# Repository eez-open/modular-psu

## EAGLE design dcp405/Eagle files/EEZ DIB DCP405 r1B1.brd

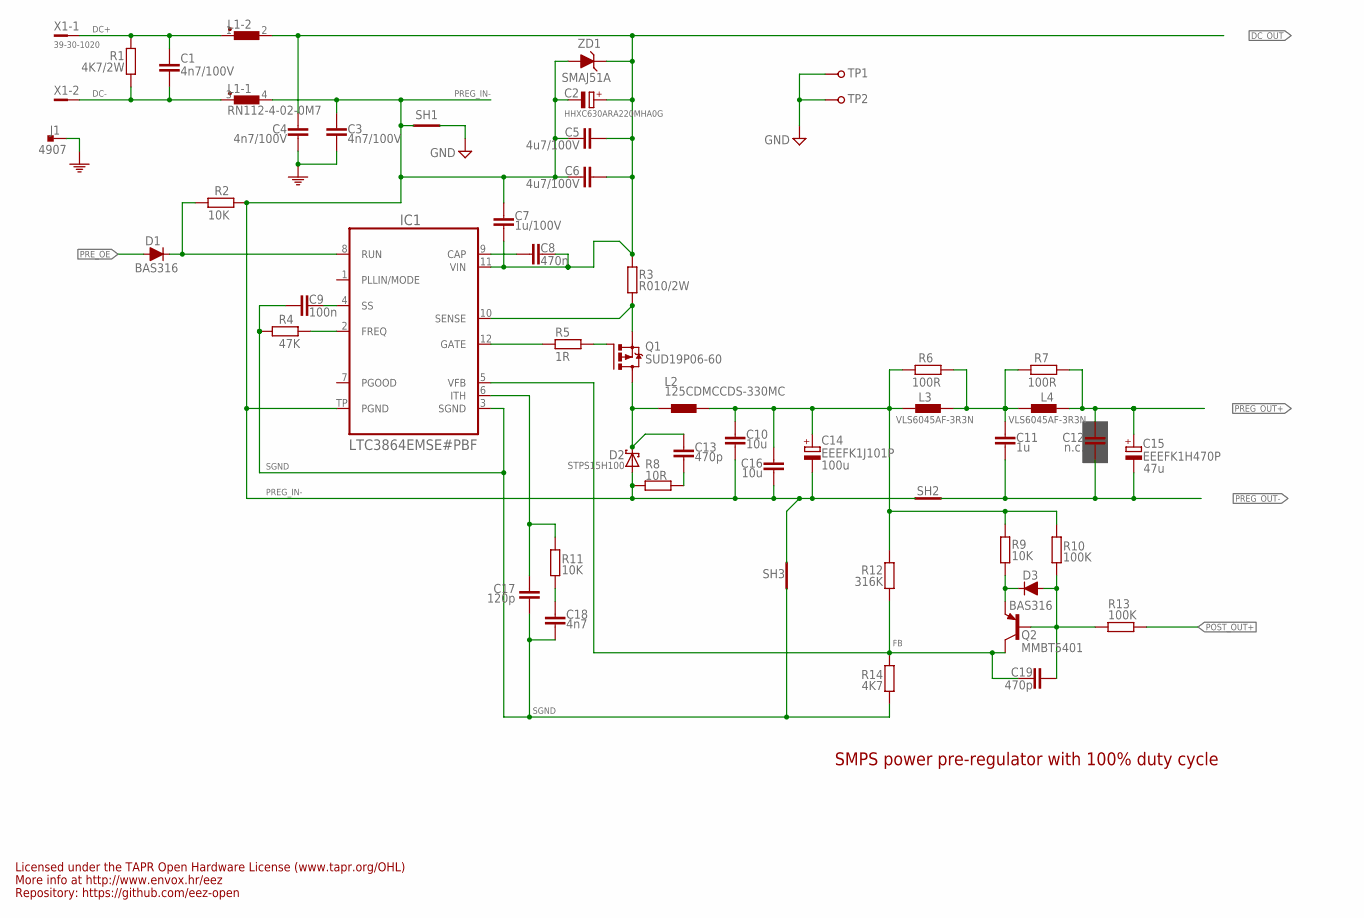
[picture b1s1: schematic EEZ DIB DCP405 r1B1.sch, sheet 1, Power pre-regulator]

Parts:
C1, C3, C4: 4n7/100V; C1206
C2: HHXC630ARA220MHA0G; CAPAE830X1050N
C5, C6: 4u7/100V; C1210
C7: 1u/100V; C1206
C8: 470n; C0805
C9: 100n; C0603
C10, C16: 10u; C1210
C11: 1u; C0805
C12: n.c.; C0805
C13, C19: 470p; C0805
C14: EEEFK1J101P; CAPAE1030X1050N
C15: EEEFK1H470P; CAPAE830X1050N
C17: 120p; C0805
C18: 4n7; C0805
D1, D3: BAS316; SOD323-R
D2: STPS15H100; TO252-L
IC1: LTC3864EMSE#PBF; LTC_05-08-1666
J1: 4907; PCB_TAB-4907
L1: RN112-4-02-0M7; RN112
L2: 125CDMCCDS-330MC; 125CDMCC/DS
L3, L4: VLS6045AF-3R3N; COILCRAFT_HPI0630
Q1: SUD19P06-60; TO229P990X239-3N
Q2: MMBT5401; SOT23-BEC
R1: 4K7/2W; R2512
R2, R9, R11: 10K; R0805
R3: R010/2W; R2512
R4: 47K; R0805
R5: 1R; R0805
R6, R7: 100R; R0805
R8: 10R; R1206
R10, R13: 100K; R0805
R12: 316K; R0805
R14: 4K7; R0805
SH1: SHORTNOHOLE; SHORT_NOHOLE
SH2: Pgnd to Pout- short; SHORT_NOHOLE
SH3: Sgnd to Pgnd short; SHORT_NOHOLE
TP1, TP2: PCB_TEST_TABSHIELD; PCB_SHIELD_TAB
X1: 39-30-1020; MINIFIT_39301020
ZD1: SMAJ51A; DO214AA

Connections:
DC+: C1.2, L1.1, R1.2, X1.1
DC-: C1.1, L1.3 (1), R1.1, X1.2
DC_OUT: C2.+, C4.2, C5.1, C6.1, C7.1, C8.2, IC1.11 (VIN), L1.2, R3.1, ZD1.C; also elsewhere on the board
FB: C19.1, IC1.5 (VFB), Q2.C, R12.2, R14.1
GND: SH1.2 (GND_B), TP1.1, TP2.1; also elsewhere on the board
L_OUT: C10.1, C14.+, C16.1, L2.2, L3.1, R6.1, R9.1, R10.1, R12.1
unnamed: D3.C, Q2.E, R9.2
unnamed: C18.1, R11.1
unnamed: D1.C, IC1.8 (RUN), R2.2
unnamed: C17.1, IC1.6 (ITH), R11.2
unnamed: C8.1, IC1.9 (CAP)
unnamed: IC1.2 (FREQ), R4.1
unnamed: C9.2, IC1.4 (SS)
unnamed: Q1.1 (G), R5.2
unnamed: IC1.12 (GATE), R5.1
unnamed: C11.1, L3.2, L4.1, R6.2, R7.1
unnamed: C13.2, R8.2
unnamed: C19.2, D3.A, Q2.B, R10.2, R13.1
PE: C3.2, C4.1, J1.1, J1.2; also elsewhere on the board
POST_OUT+: R13.2; also elsewhere on the board
PREG_IN-: C2.-, C3.1, C5.2, C6.2, C7.2, C10.2, C14.-, C16.2, D2.1 (A), D2.2 (A), IC1.TP (PGND), L1.4 (2), R2.1, R8.1, SH1.1 (GND_A), SH2.2 (GND_B), SH3.2 (GND_B), ZD1.A
PREG_OUT+: C12.1, C15.+, L4.2, R7.2; also elsewhere on the board
PREG_OUT-: C11.2, C12.2, C15.-, SH2.1 (GND_A); also elsewhere on the board
PRE_OE: D1.A; also elsewhere on the board
SENSE: IC1.10 (SENSE), Q1.3 (S), R3.2
SGND: C9.1, C17.2, C18.2, IC1.3 (SGND), R4.2, R14.2, SH3.1 (GND_A)
SW: C13.1, D2.3 (C), L2.1, Q1.2 (D)

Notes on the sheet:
47u
Licensed under the TAPR Open Hardware License (www.tapr.org/OHL)
Repository: https://github.com/eez-open
More info at http://www.envox.hr/eez
SMPS power pre-regulator with 100% duty cycle
100u

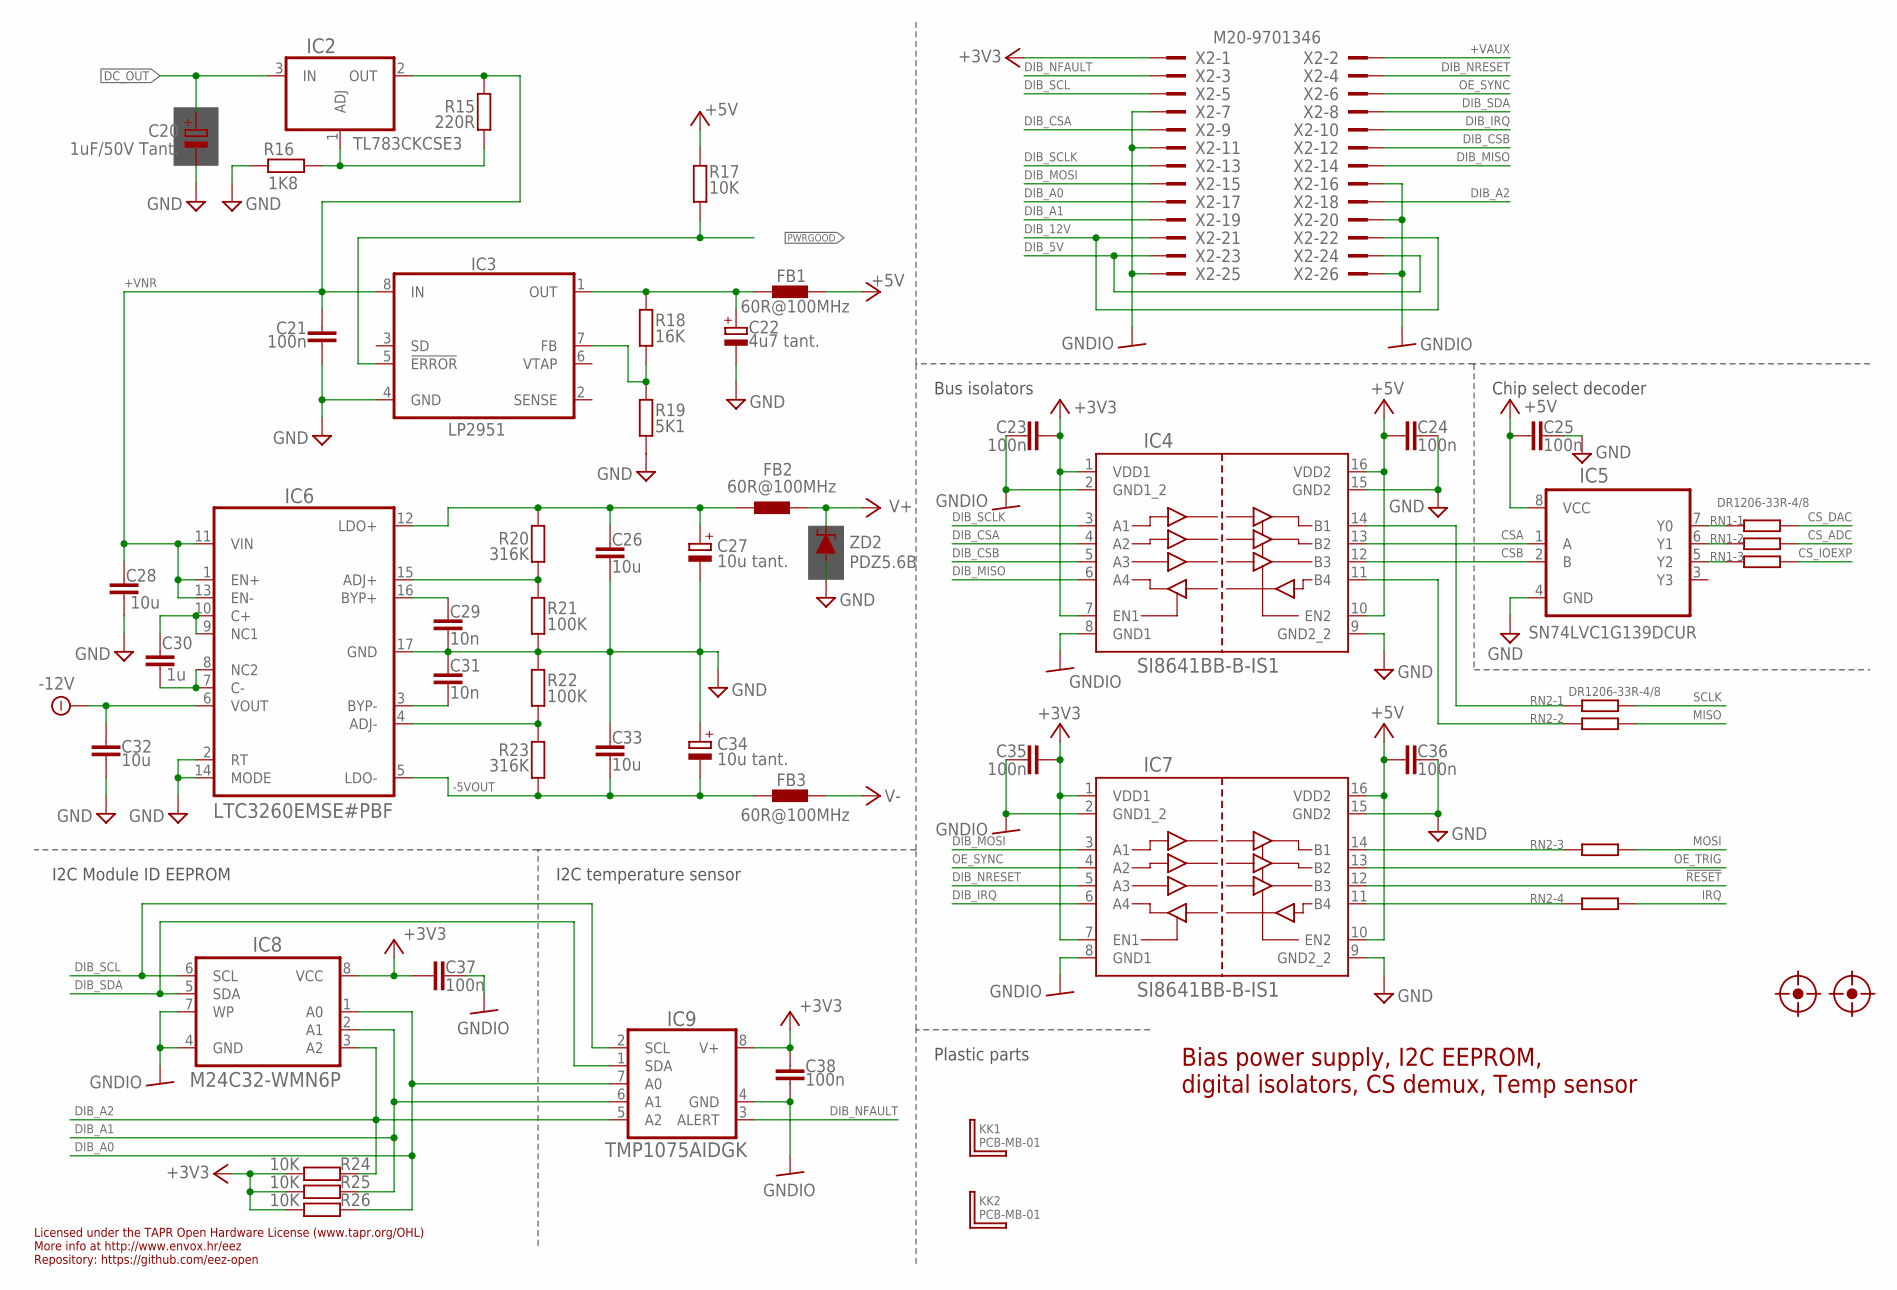
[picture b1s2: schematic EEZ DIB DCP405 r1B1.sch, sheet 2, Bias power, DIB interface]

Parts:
C20: 1uF/50V Tant.; C/6032-28R
C21, C23, C24, C25, C35, C36, C37, C38: 100n; C0603
C22: 4u7 tant.; EC1206
C26, C28, C32, C33: 10u; C1210
C27, C34: 10u tant.; EC1206
C29, C31: 10n; C0805
C30: 1u; C0805
FB1, FB2, FB3: 60R@100MHz; BEAD0603
FM1, FM2: FIDUCIAL_2; FIDUCIAL_DUAL
IC2: TL783CKCSE3; TO220H-CLR2
IC3: LP2951; SOIC127P600X175-8N
IC4, IC7: SI8641BB-B-IS1; SOIC-16
IC5: SN74LVC1G139DCUR; DCU8
IC6: LTC3260EMSE#PBF; SOP50P490X110-17N
IC8: M24C32-WMN6P; SOIC127P600X173-8N
IC9: TMP1075AIDGK; DGK8
KK1, KK2: PCB-MB-01; PCB-MB
R15: 220R; R0805
R16: 1K8; R0805
R17, R24, R25, R26: 10K; R0805
R18: 16K; R0805
R19: 5K1; R0805
R20, R23: 316K; R0805
R21, R22: 100K; R0805
RN1, RN2: DR1206-33R-4/8; CAY16
X2: M20-9701346
ZD2: PDZ5.6B; SOD323-W

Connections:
!RESET: IC7.12 (B3); also elsewhere on the board
+3V3: C23.1, C35.1, C37.2, C38.1, IC4.1 (VDD1), IC4.7 (EN1), IC7.1 (VDD1), IC7.7 (EN1), IC8.8 (VCC), IC9.8 (V+), R24.1, R25.1, R26.1, X2.1
+5V: C24.2, C25.1, C36.2, FB1.P$2 (2), IC4.10 (EN2), IC4.16 (VDD2), IC5.8 (VCC), IC7.10 (EN2), IC7.16 (VDD2), R17.1; also elsewhere on the board
+5VOUT: C26.1, C27.+, FB2.P$1 (1), IC6.12 (LDO+), R20.1
+VAUX: X2.2
+VNR: C21.1, C28.1, IC2.2 (OUT), IC3.8 (IN), IC6.1 (EN+), IC6.11 (VIN), IC6.13 (EN-), R15.1
-5VOUT: C33.2, C34.-, FB3.P$1 (1), IC6.5 (LDO-), R23.2
-12V: C32.1, IC6.6 (VOUT); also elsewhere on the board
CSA: IC4.13 (B2), IC5.1 (A)
CSB: IC4.12 (B3), IC5.2 (B)
CS_ADC: RN1.7 (2); also elsewhere on the board
CS_DAC: RN1.8 (2); also elsewhere on the board
CS_IOEXP: RN1.6 (2); also elsewhere on the board
DC_OUT: C20.+, IC2.3 (IN); also elsewhere on the board
DIB_5V: X2.23, X2.24
DIB_12V: X2.21, X2.22
DIB_A0: IC8.1 (A0), IC9.7 (A0), R26.2, X2.17
DIB_A1: IC8.2 (A1), IC9.6 (A1), R25.2, X2.19
DIB_A2: IC8.3 (A2), IC9.5 (A2), R24.2, X2.18
DIB_CSA: IC4.4 (A2), X2.9
DIB_CSB: IC4.5 (A3), X2.12
DIB_IRQ: IC7.6 (A4), X2.10
DIB_MISO: IC4.6 (A4), X2.14
DIB_MOSI: IC7.3 (A1), X2.15
DIB_NFAULT: IC9.3 (ALERT), X2.3
DIB_NRESET: IC7.5 (A3), X2.4
DIB_SCL: IC8.6 (SCL), IC9.2 (SCL), X2.5
DIB_SCLK: IC4.3 (A1), X2.13
DIB_SDA: IC8.5 (SDA), IC9.1 (SDA), X2.8
GND: C20.-, C21.2, C22.-, C24.1, C25.2, C26.2, C27.-, C28.2, C29.1, C31.1, C32.2, C33.1, C34.+, C36.1, IC3.4 (GND), IC4.9 (GND2_2), IC4.15 (GND2), IC5.4 (GND), IC6.2 (RT), IC6.14 (MODE), IC6.17 (GND), IC7.9 (GND2_2), IC7.15 (GND2), R16.2, R19.2, R21.2, R22.1, ZD2.A; also elsewhere on the board
GNDIO: C23.2, C35.2, C37.1, C38.2, IC4.2 (GND1_2), IC4.8 (GND1), IC7.2 (GND1_2), IC7.8 (GND1), IC8.4 (GND), IC8.7 (WP), IC9.4 (GND), X2.7, X2.11, X2.16, X2.20, X2.25, X2.26
IRQ: RN2.5 (2); also elsewhere on the board
MISO: RN2.7 (2); also elsewhere on the board
MOSI: RN2.6 (2); also elsewhere on the board
unnamed: IC5.5 (Y2), RN1.3 (1)
unnamed: IC5.7 (Y0), RN1.1
unnamed: IC4.11 (B4), RN2.2 (1)
unnamed: IC7.11 (B4), RN2.4 (1)
unnamed: IC5.6 (Y1), RN1.2 (1)
unnamed: IC6.15 (ADJ+), R20.2, R21.1
unnamed: C30.1, IC6.9 (NC1), IC6.10 (C+)
unnamed: C30.2, IC6.7 (C-), IC6.8 (NC2)
unnamed: C29.2, IC6.16 (BYP+)
unnamed: IC6.4 (ADJ-), R22.2, R23.1
unnamed: C31.2, IC6.3 (BYP-)
unnamed: IC7.14 (B1), RN2.3 (1)
unnamed: IC3.7 (FB), R18.2, R19.1
unnamed: IC4.14 (B1), RN2.1
unnamed: C22.+, FB1.P$1 (1), IC3.1 (OUT), R18.1
OE_SYNC: IC7.4 (A2), X2.6
OE_TRIG: IC7.13 (B2); also elsewhere on the board
PWRGOOD: IC3.5 (!ERROR), R17.2; also elsewhere on the board
SCLK: RN2.8 (2); also elsewhere on the board
TL783_ADJ: IC2.1 (ADJ), R15.2, R16.1
V+: FB2.P$2 (2), ZD2.C; also elsewhere on the board
V-: FB3.P$2 (2); also elsewhere on the board

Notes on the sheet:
Licensed under the TAPR Open Hardware License (www.tapr.org/OHL)
Repository: https://github.com/eez-open
More info at http://www.envox.hr/eez
I2C Module ID EEPROM
Bus isolators
Bias power supply, I2C EEPROM, digital isolators, CS demux, Temp sensor
Plastic parts
Chip select decoder
I2C temperature sensor

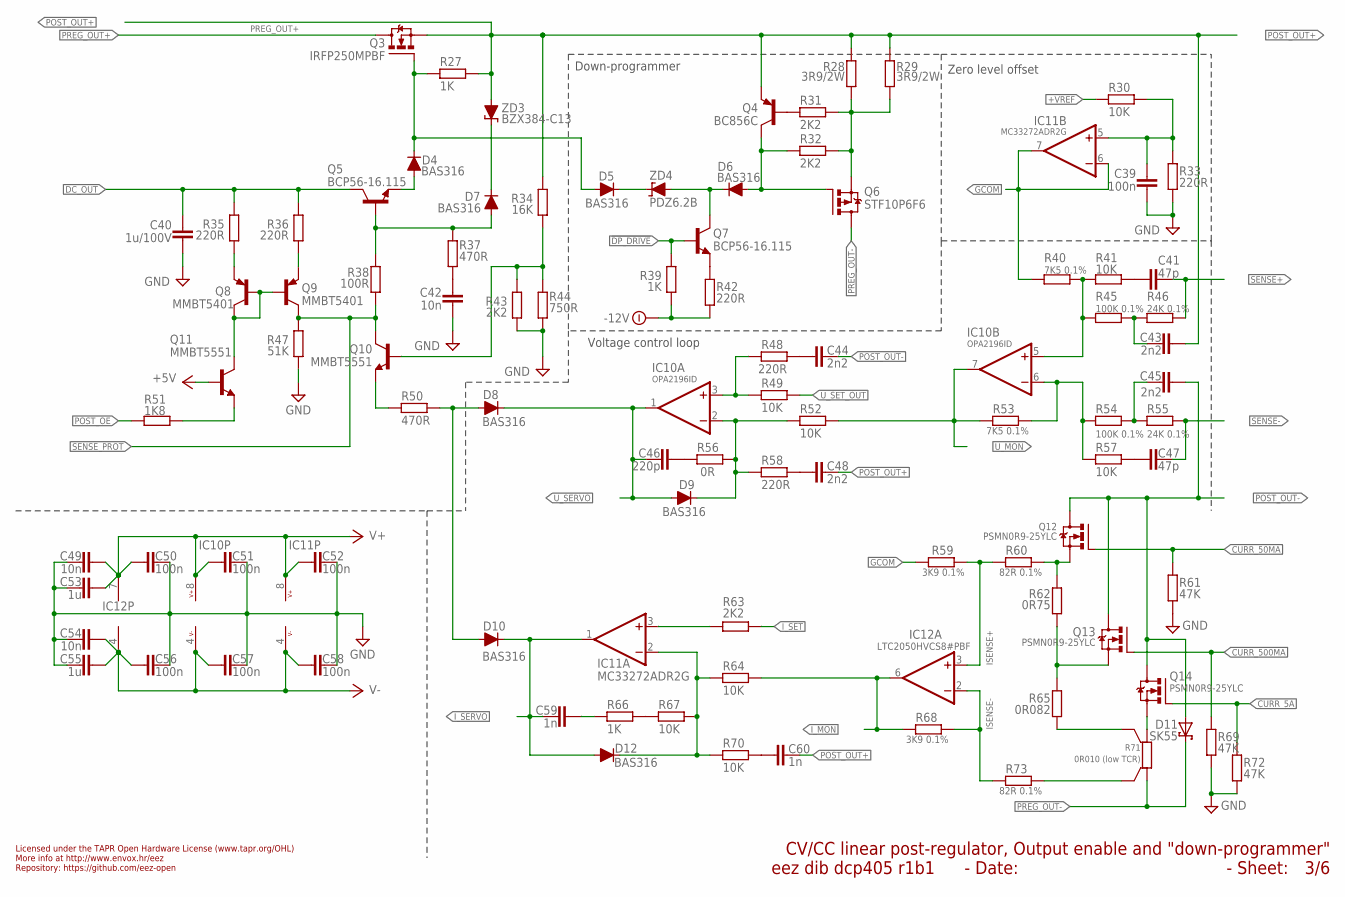
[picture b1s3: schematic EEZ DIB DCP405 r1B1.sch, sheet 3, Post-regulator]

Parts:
C39, C50, C51, C52, C56, C57, C58: 100n; C0603
C40: 1u/100V; C1206
C41, C47: 47p; C0805
C42, C49, C54: 10n; C0805
C43, C44, C45, C48: 2n2; C0805
C46: 220p; C0805
C53, C55: 1u; C0805
C59, C60: 1n; C0805
D4, D5, D6, D7, D8, D9, D10, D12: BAS316; SOD323-R
D11: SK55; SMB
IC10: OPA2196ID; SOIC127P600X173-8N
IC11: MC33272ADR2G; SOIC127P600X173-8N
IC12: LTC2050HVCS8#PBF; SOIC127P600X173-8N
Q3: IRFP250MPBF; TO247BH-CLR2
Q4: BC856C; SOT23-BEC
Q5, Q7: BCP56-16.115; SOT230P700X180-4N
Q6: STF10P6F6; TO220H-CLR2
Q8, Q9: MMBT5401; SOT23-BEC
Q10, Q11: MMBT5551; SOT23-BEC
Q12, Q13, Q14: PSMN0R9-25YLC; SOT669
R27, R39, R66: 1K; R0805
R28, R29: 3R9/2W; R2512
R30, R41, R49, R52, R57, R64, R67, R70: 10K; R0805
R31, R32, R43, R63: 2K2; R0805
R33, R35, R36, R42, R48, R58: 220R; R0805
R34: 16K; R0805
R37, R50: 470R; R0805
R38: 100R; R0805
R40, R53: 7K5 0.1%; R0805
R44: 750R; R0805
R45, R54: 100K 0.1%; R0805
R46, R55: 24K 0.1%; R0805
R47: 51K; R0805
R51: 1K8; R0805
R56: 0R; R0805
R59, R68: 3K9 0.1%; R0805
R60, R73: 82R 0.1%; R0805
R61, R69, R72: 47K; R0805
R62: 0R75; R1206
R65: 0R082; R1210
R71: 0R010 (low TCR); R_H2728
ZD3: BZX384-C13; SOD323-W
ZD4: PDZ6.2B; SOD323-W

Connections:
5A_S: Q14.1 (S), Q14.2 (S), Q14.3 (S), R71.2
50MA_S: Q12.1 (S), Q12.2 (S), Q12.3 (S), R60.1, R62.1
500MA_S: Q13.1 (S), Q13.2 (S), Q13.3 (S), R62.2, R65.2
!DP_DRIVE: Q7.1 (B), R39.1; also elsewhere on the board
+5V: Q11.B; also elsewhere on the board
+VREF: R30.1; also elsewhere on the board
-12V: R39.2, R42.2; also elsewhere on the board
CURR_5A: Q14.4 (G), R72.2; also elsewhere on the board
CURR_50MA: Q12.4 (G), R61.2; also elsewhere on the board
CURR_500MA: Q13.4 (G), R69.2; also elsewhere on the board
DC_OUT: C40.1, Q5.2 (C), Q5.4 (C), R35.2, R36.2; also elsewhere on the board
DP_S: Q6.3 (S), R28.1, R29.1, R31.1, R32.1
GCOM: IC11.6 (-IN), IC11.7 (OUT), R40.1, R59.1
GND: C39.2, C40.2, C42.2, C49.1, C50.2, C51.1, C52.1, C53.1, C54.1, C55.1, C56.2, C57.1, C58.1, R33.2, R43.1, R44.1, R47.1, R61.1, R69.1, R72.1; also elsewhere on the board
ISENSE+: IC12.3 (+IN), R59.2, R60.2
ISENSE-: IC12.2 (-IN), R68.1, R73.2
I_MON: IC12.6 (OUT), R64.1, R68.2; also elsewhere on the board
I_SERVO: C59.2, D10.C, D12.A, IC11.1 (OUT); also elsewhere on the board
I_SET: R63.1; also elsewhere on the board
LOOP_CTRL: D8.A, D10.A, R50.1
unnamed: R65.1, R71.2S
unnamed: C46.1, R56.2
unnamed: IC11.3 (+IN), R63.2
unnamed: IC10.3 (+IN), R48.2, R49.2
unnamed: D9.C, IC10.2 (-IN), R52.2, R56.1, R58.2
unnamed: C45.1, R54.2, R55.1
unnamed: C41.2, R41.1
unnamed: C47.2, R57.1
unnamed: C60.2, R70.1
unnamed: D12.C, IC11.2 (-IN), R64.2, R67.2, R70.2
unnamed: C44.2, R48.1
unnamed: C48.2, R58.1
unnamed: D4.C, D5.A, Q3.1 (G), R27.1
unnamed: D4.A, Q5.3 (E)
unnamed: D7.A, Q5.1 (B), R37.2, R38.1
unnamed: C42.1, R37.1
unnamed: Q10.B, R34.1, R43.2, R44.2
unnamed: Q7.3 (E), R42.1
unnamed: Q4.B, R31.2
unnamed: C39.1, IC11.5 (+IN), R30.2, R33.1
unnamed: C43.1, R45.2, R46.1
unnamed: D7.C, ZD3.C
unnamed: D5.C, ZD4.C
unnamed: Q10.E, R50.2
unnamed: D6.A, Q4.C, Q6.1 (G), R32.2
unnamed: IC10.5 (+IN), R40.2, R41.2, R45.1
unnamed: IC10.6 (-IN), R53.2, R54.1, R57.2
unnamed: R66.2, R67.1
unnamed: C59.1, R66.1
unnamed: Q9.E, R36.1
unnamed: Q8.E, R35.1
unnamed: Q11.E, R51.2
unnamed: R71.1S, R73.1
POST_OE: R51.1; also elsewhere on the board
POST_OUT+: C43.2, C48.1, C60.1, Q3.3 (S), Q4.E, R27.2, R28.2, R29.2, R34.2, ZD3.A; also elsewhere on the board
POST_OUT-: C44.1, C45.2, D11.A, Q12.MB (D), Q13.MB (D), Q14.MB (D); also elsewhere on the board
PREG_OUT+: Q3.2 (D); also elsewhere on the board
PREG_OUT-: D11.C, Q6.2 (D), R71.1; also elsewhere on the board
Q6C: D6.C, Q7.2 (C), Q7.4 (C), ZD4.A
Q7C: Q8.B, Q8.C, Q9.B, Q11.C
SENSE+: C41.1, R46.2; also elsewhere on the board
SENSE-: C47.1, R55.2; also elsewhere on the board
SENSE_PROT: Q9.C, Q10.C, R38.2, R47.2; also elsewhere on the board
U_MON: IC10.7 (OUT), R52.1, R53.1; also elsewhere on the board
U_SERVO: C46.2, D8.C, D9.A, IC10.1 (OUT); also elsewhere on the board
U_SET_OUT: R49.1; also elsewhere on the board
V+: C49.2, C50.1, C51.2, C52.2, C53.2, IC10.8 (V+), IC11.8 (V+), IC12.7 (V+); also elsewhere on the board
V-: C54.2, C55.2, C56.1, C57.2, C58.2, IC10.4 (V-), IC11.4 (V-), IC12.4 (V-); also elsewhere on the board

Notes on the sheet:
Voltage control loop
Down-programmer
Licensed under the TAPR Open Hardware License (www.tapr.org/OHL)
Repository: https://github.com/eez-open
More info at http://www.envox.hr/eez
Zero level offset
CV/CC linear post-regulator, Output enable and "down-programmer"
- Sheet:
- Date:

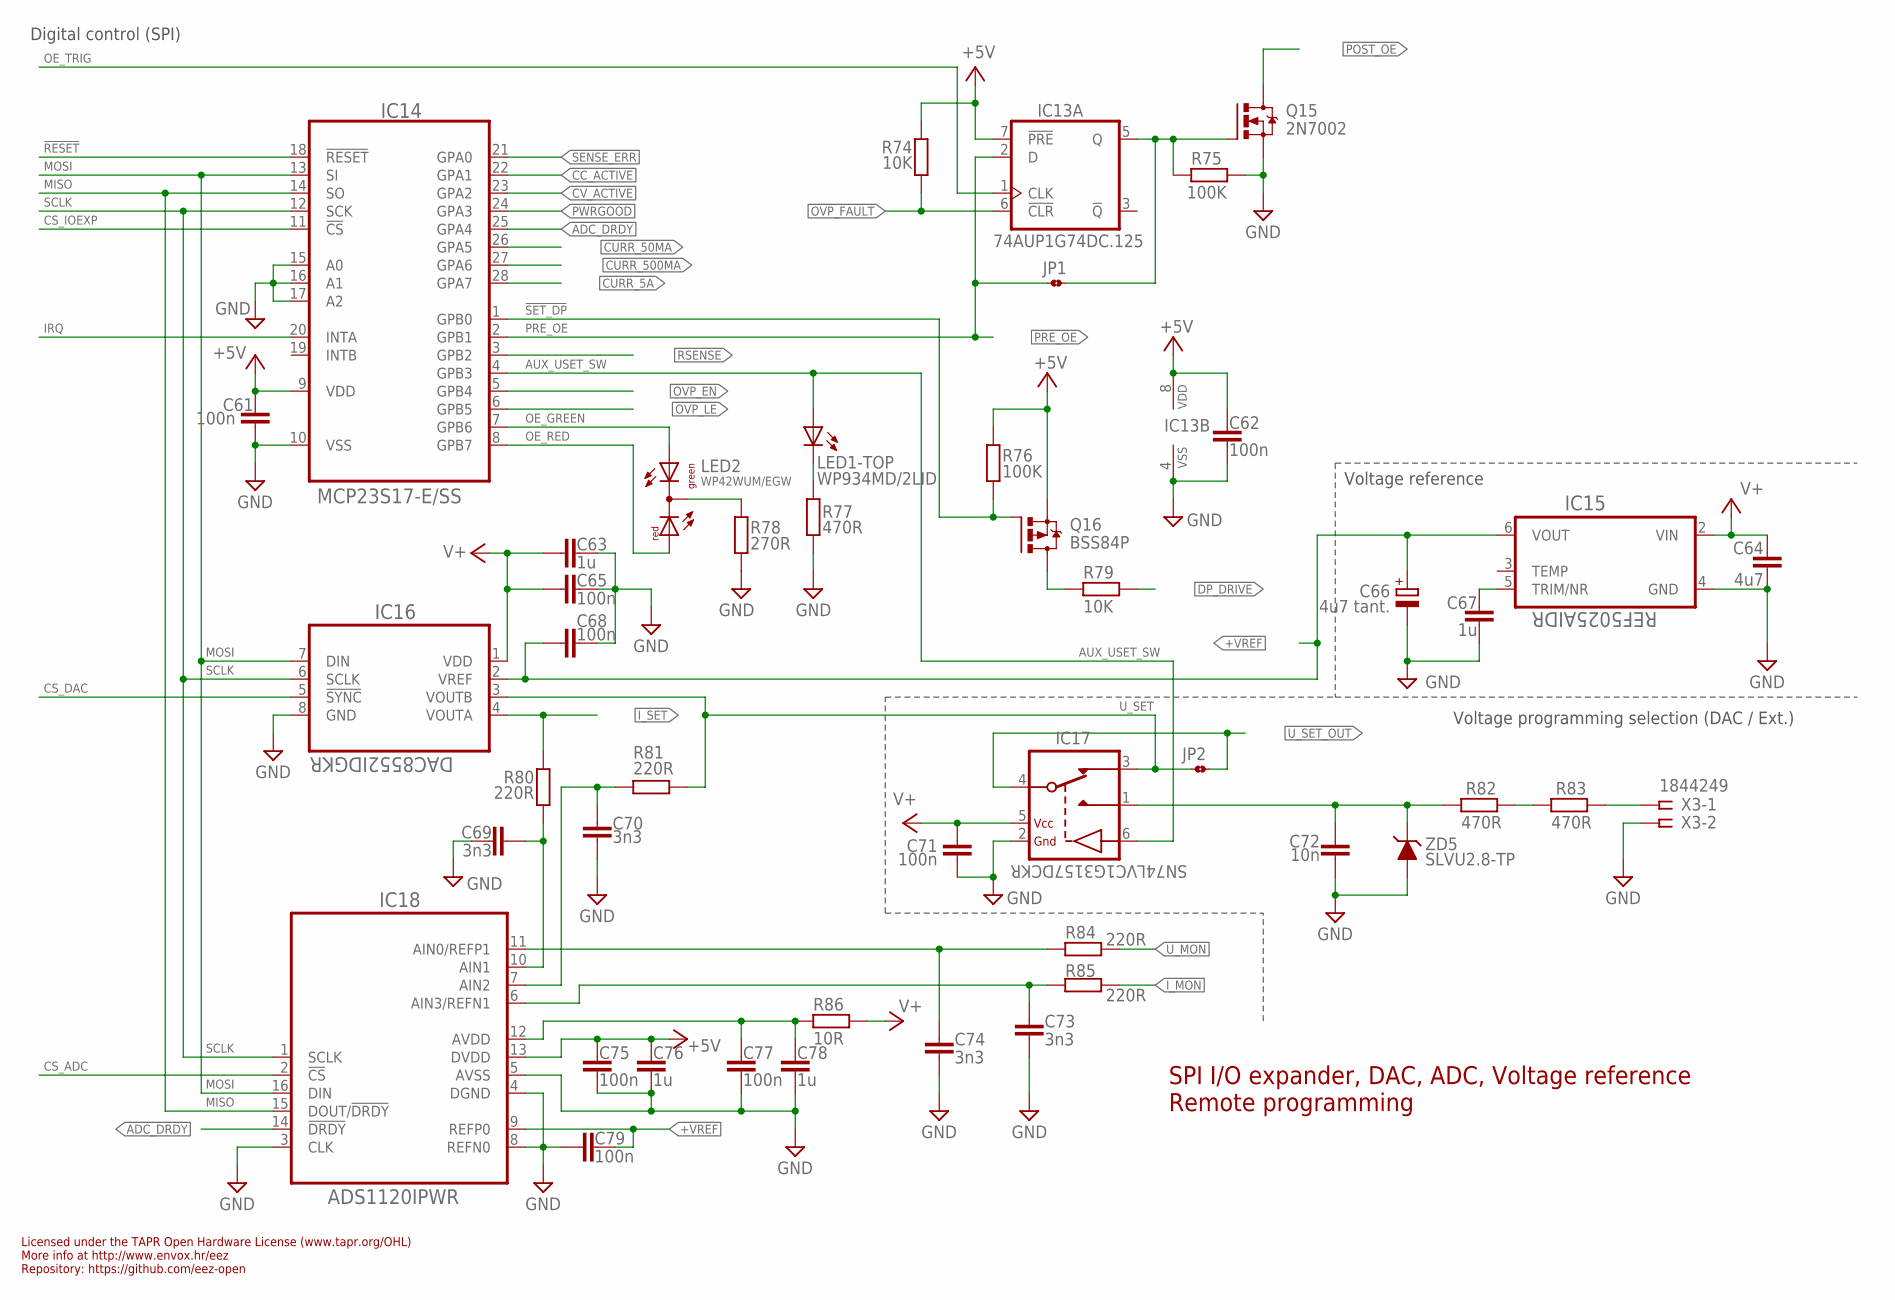
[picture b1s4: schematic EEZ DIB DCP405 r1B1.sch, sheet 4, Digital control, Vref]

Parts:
C61, C62, C65, C68, C71, C75, C77, C79: 100n; C0603
C63, C67, C76, C78: 1u; C0805
C64: 4u7; C1206
C66: 4u7 tant.; EC1206
C69, C70, C73, C74: 3n3; C0805
C72: 10n; C0805
IC13: 74AUP1G74DC.125; DCU8
IC14: MCP23S17-E/SS; SOP65P780X200-28N
IC15: REF5025AIDR; SOIC127P600X175-8N
IC16: DAC8552IDGKR; DGK8-M
IC17: SN74LVC1G3157DCKR; SOT65P210X110-6N
IC18: ADS1120IPWR; PW(R-PDSO-G16)
JP1, JP2: JP2-CUT
LED1: WP934MD/2LID; WP934MD
LED2: WP42WUM/EGW; L-42WUM-1EGWT
Q15: 2N7002; SOT103P240X110-3N; MPN 2N7002-7-F
Q16: BSS84P; SOT95P237X112-3N
R74, R79: 10K; R0805
R75, R76: 100K; R0805
R77, R82, R83: 470R; R0805
R78: 270R; R0805
R80, R81, R84, R85: 220R; R0805
R86: 10R; R1206
X3: 1844249; MC1,5/5-G-3,5
ZD5: SLVU2.8-TP; SOT23

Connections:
!ADC_DRDY: IC14.25 (GPA4), IC18.14 (!DRDY)
!DP_DRIVE: R79.1; also elsewhere on the board
!OVP_FAULT: IC13.6 (!CLR), R74.2; also elsewhere on the board
!OVP_LE: IC14.6 (GPB5); also elsewhere on the board
!RESET: IC14.18 (!RESET); also elsewhere on the board
!SET_DP: IC14.1 (GPB0), Q16.1 (G), R76.2
+5V: C61.1, C62.2, C75.2, C76.2, IC13.7 (!PRE), IC13.8 (VDD), IC14.9 (VDD), IC18.13 (DVDD), Q16.2 (S), R74.1, R76.1; also elsewhere on the board
+VREF: C66.+, C68.2, C79.2, IC15.6 (VOUT), IC16.2 (VREF), IC18.9 (REFP0); also elsewhere on the board
AUX_IN: C72.2, IC17.1 (NO), R82.1, ZD5.3 (C)
AUX_USET_SW: IC14.4 (GPB3), IC17.6 (CTRL), LED1.TA (A)
CC_ACTIVE: IC14.22 (GPA1); also elsewhere on the board
CS_ADC: IC18.2 (!CS); also elsewhere on the board
CS_DAC: IC16.5 (!SYNC); also elsewhere on the board
CS_IOEXP: IC14.11 (!CS); also elsewhere on the board
CURR_5A: IC14.28 (GPA7); also elsewhere on the board
CURR_50MA: IC14.26 (GPA5); also elsewhere on the board
CURR_500MA: IC14.27 (GPA6); also elsewhere on the board
CV_ACTIVE: IC14.23 (GPA2); also elsewhere on the board
DP_LED: Q16.3 (D), R79.2
GND: C61.2, C62.1, C63.2, C64.2, C65.1, C66.-, C67.2, C68.1, C69.1, C70.1, C71.2, C72.1, C73.2, C74.1, C75.1, C76.1, C77.1, C78.1, C79.1, IC13.4 (VSS), IC14.10 (VSS), IC14.15 (A0), IC14.16 (A1), IC14.17 (A2), IC15.4 (GND), IC16.8 (GND), IC17.2 (GND), IC18.3 (CLK), IC18.4 (DGND), IC18.5 (AVSS), IC18.8 (REFN0), Q15.2 (S), R75.1, R77.1, R78.2, X3.2, ZD5.1 (A), ZD5.2 (A); also elsewhere on the board
IRQ: IC14.20 (INTA); also elsewhere on the board
I_MON: R85.1; also elsewhere on the board
I_SET: IC16.4 (VOUTA), R80.1; also elsewhere on the board
MISO: IC14.14 (SO), IC18.15 (DOUT/!DRDY); also elsewhere on the board
MOSI: IC14.13 (SI), IC16.7 (DIN), IC18.16 (DIN); also elsewhere on the board
unnamed: LED2.CC (C), R78.1
unnamed: R82.2, R83.1
unnamed: R83.2, X3.1
unnamed: IC13.5 (Q), JP1.2, Q15.1 (G), R75.2
unnamed: C77.2, C78.2, IC18.12 (AVDD), R86.2
unnamed: C67.1, IC15.5 (TRIM/NR)
unnamed: C69.2, IC18.10 (AIN1), R80.2
unnamed: C74.2, IC18.11 (AIN0/REFP1), R84.2
unnamed: C70.2, IC18.7 (AIN2), R81.2
unnamed: C73.1, IC18.6 (AIN3/REFN1), R85.2
unnamed: LED1.TC (C), R77.2
OE_GREEN: IC14.7 (GPB6), LED2.GREEN (AG)
OE_RED: IC14.8 (GPB7), LED2.RED (AR)
OE_TRIG: IC13.1 (CLK); also elsewhere on the board
OVP_EN: IC14.5 (GPB4); also elsewhere on the board
POST_OE: Q15.3 (D); also elsewhere on the board
PRE_OE: IC13.2 (D), IC14.2 (GPB1), JP1.1; also elsewhere on the board
PWRGOOD: IC14.24 (GPA3); also elsewhere on the board
RSENSE: IC14.3 (GPB2); also elsewhere on the board
SCLK: IC14.12 (SCK), IC16.6 (SCLK), IC18.1 (SCLK); also elsewhere on the board
SENSE_ERR: IC14.21 (GPA0); also elsewhere on the board
U_MON: R84.1; also elsewhere on the board
U_SET: IC16.3 (VOUTB), IC17.3 (NC), JP2.1, R81.1; also elsewhere on the board
U_SET_OUT: IC17.4 (COM), JP2.2; also elsewhere on the board
V+: C63.1, C64.1, C65.2, C71.1, IC15.2 (VIN), IC16.1 (VDD), IC17.5 (VDD), R86.1; also elsewhere on the board

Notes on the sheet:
SPI I/O expander, DAC, ADC, Voltage reference
Digital control (SPI)
Voltage reference
Licensed under the TAPR Open Hardware License (www.tapr.org/OHL)
Repository: https://github.com/eez-open
More info at http://www.envox.hr/eez
Remote programming
Voltage programming selection (DAC / Ext.)

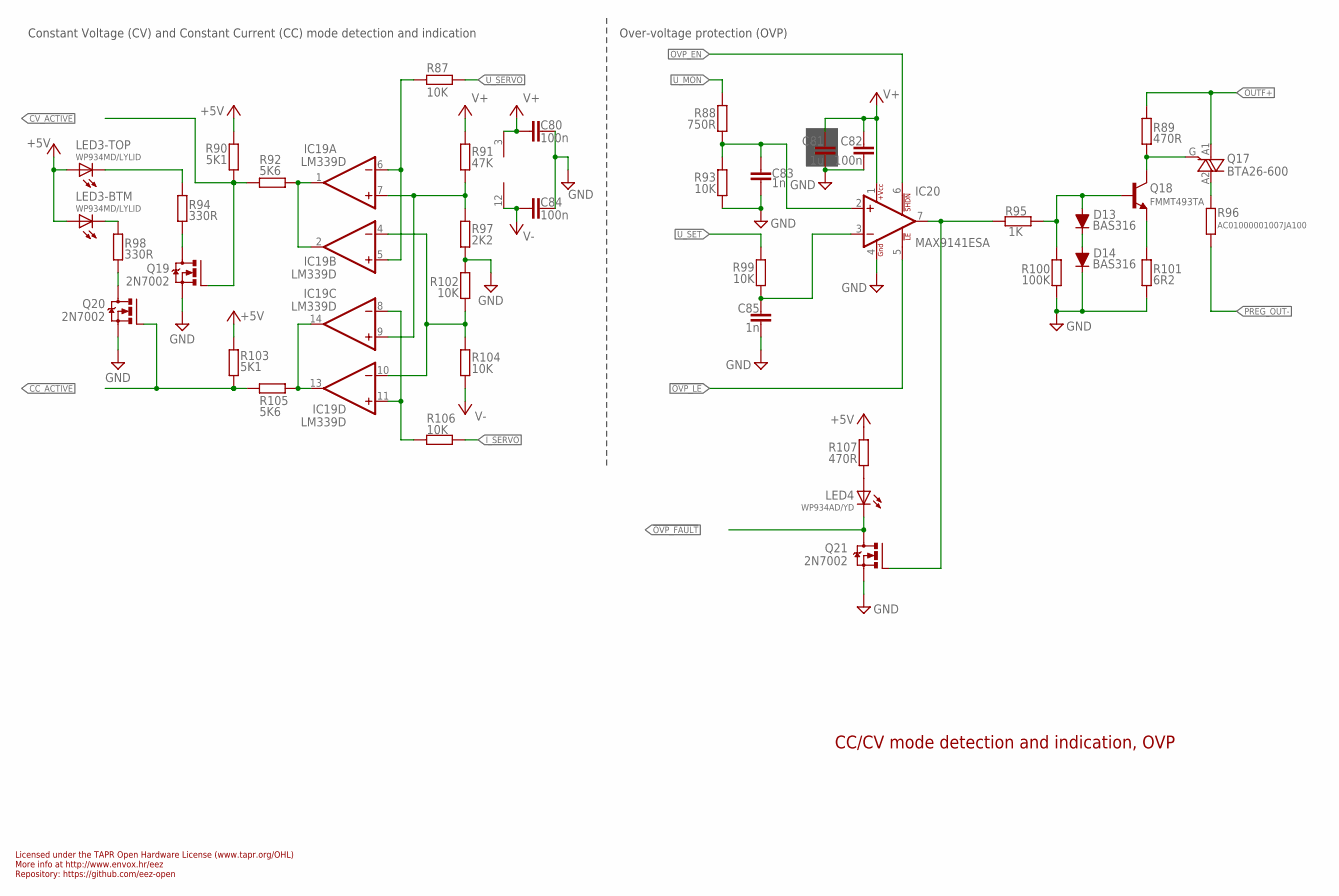
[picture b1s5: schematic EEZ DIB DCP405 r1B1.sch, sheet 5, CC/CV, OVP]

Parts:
C80, C82, C84: 100n; C0603
C81: 1u; C0805
C83, C85: 1n; C0805
D13, D14: BAS316; SOD323-R
IC19: LM339D; SOIC127P600X175-14N
IC20: MAX9141ESA; SOIC127P600X173-8N
LED3: WP934MD/LYLID; WP934MD
LED4: WP934AD/YD; WP934AD
Q17: BTA26-600; TOP3_TRIAC_NOHOLE
Q18: FMMT493TA; SOT23-BEC
Q19, Q20: 2N7002; SOT103P240X110-3N
Q21: 2N7002; SOT103P240X110-3N; MPN 2N7002-7-F
R87, R93, R99, R102, R104, R106: 10K; R0805
R88: 750R; R0805
R89, R107: 470R; R0805
R90, R103: 5K1; R0805
R91: 47K; R0805
R92, R105: 5K6; R0805
R94, R98: 330R; R0805
R95: 1K; R0805
R96: AC01000001007JA100; 0411/15
R97: 2K2; R0805
R100: 100K; R0805
R101: 6R2; R0805

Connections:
!OVP_FAULT: LED4.C, Q21.3 (D); also elsewhere on the board
!OVP_LE: IC20.5 (!LE); also elsewhere on the board
+5V: LED3.BA (A), LED3.TA (A), R90.2, R103.2, R107.1; also elsewhere on the board
CC_ACTIVE: Q20.1 (G), R103.1, R105.2; also elsewhere on the board
CC_LED: LED3.BC (C), R98.2
CV_ACTIVE: Q19.1 (G), R90.1, R92.2; also elsewhere on the board
CV_LED: LED3.TC (C), R94.1
GND: C80.1, C81.2, C82.1, C83.1, C84.1, C85.1, D14.C, IC20.4 (GND), Q19.2 (S), Q20.2 (S), Q21.2 (S), R93.2, R97.1, R100.1, R101.1, R102.2; also elsewhere on the board
I_SERVO: R106.1; also elsewhere on the board
unnamed: LED4.A, R107.2
unnamed: IC20.7 (OUT), Q21.1 (G), R95.2
unnamed: Q17.A2, R96.2
unnamed: Q17.G, Q18.C, R89.1
unnamed: Q18.E, R101.2
unnamed: D13.C, D14.A
unnamed: D13.A, Q18.B, R95.1, R100.2
unnamed: C85.2, IC20.3 (-IN), R99.2
unnamed: C83.2, IC20.2 (+IN), R88.2, R93.1
unnamed: Q20.3 (D), R98.1
unnamed: IC19.1 (OUT), IC19.2 (OUT), R92.1
unnamed: IC19.13 (OUT), IC19.14 (OUT), R105.1
unnamed: Q19.3 (D), R94.2
unnamed: IC19.5 (+IN), IC19.6 (-IN), R87.2
unnamed: IC19.8 (-IN), IC19.11 (+IN), R106.2
unnamed: IC19.7 (+IN), IC19.9 (+IN), R91.1, R97.2
unnamed: IC19.4 (-IN), IC19.10 (-IN), R102.1, R104.2
OUTF+: Q17.A1, R89.2; also elsewhere on the board
OVP_EN: IC20.6 (!SHDN); also elsewhere on the board
PREG_OUT-: R96.1; also elsewhere on the board
U_MON: R88.1; also elsewhere on the board
U_SERVO: R87.1; also elsewhere on the board
U_SET: R99.1; also elsewhere on the board
V+: C80.2, C81.1, C82.2, IC19.3 (V+), IC20.1 (+VCC), R91.2; also elsewhere on the board
V-: C84.2, IC19.12 (GND), R104.1; also elsewhere on the board

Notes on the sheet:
Licensed under the TAPR Open Hardware License (www.tapr.org/OHL)
Repository: https://github.com/eez-open
More info at http://www.envox.hr/eez
CC/CV mode detection and indication, OVP
Constant Voltage (CV) and Constant Current (CC) mode detection and indication
Over-voltage protection (OVP)

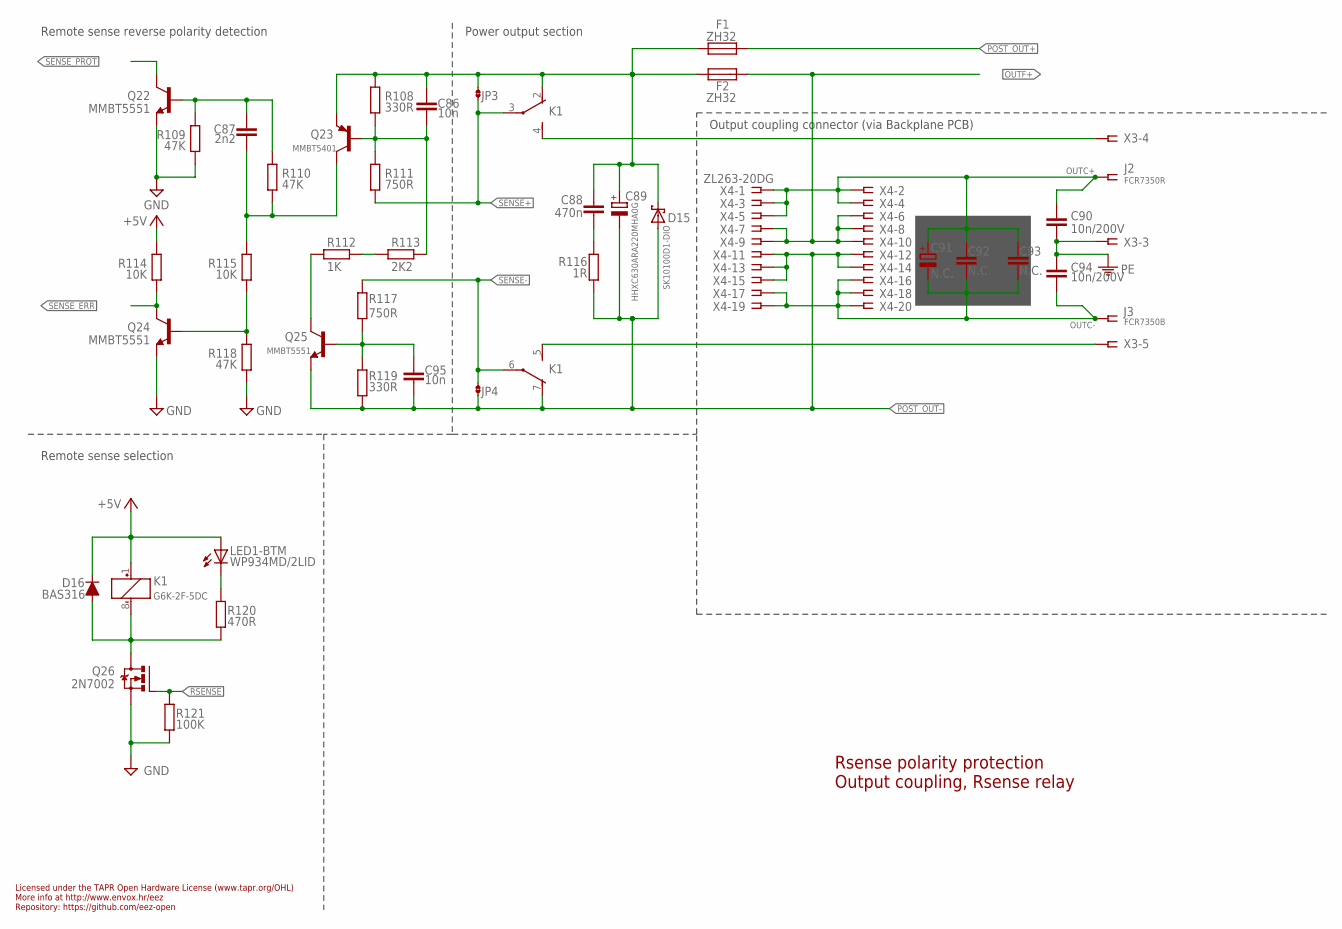
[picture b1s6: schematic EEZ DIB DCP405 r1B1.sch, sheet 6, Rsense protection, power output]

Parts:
C86, C95: 10n; C0805
C87: 2n2; C0805
C88: 470n; C1206
C89: HHXC630ARA220MHA0G; CAPAE830X1050N
C90, C94: 10n/200V; C1206
C91: N.C.; ECAP2/5
C92, C93: N.C.; C0805
D15: SK10100D1-DIO; TO252-L
D16: BAS316; SOD323-R
F1, F2: ZH32
J2: FCR7350R; S16N-PC
J3: FCR7350B; S16N-PC
JP3, JP4: JP2-CUT
K1: G6K-2F-5DC; G6K-2F; MPN G6K-2F DC24
LED1: WP934MD/2LID; WP934MD
Q22, Q24, Q25: MMBT5551; SOT23-BEC
Q23: MMBT5401; SOT23-BEC
Q26: 2N7002; SOT103P240X110-3N; MPN 2N7002-7-F
R108, R119: 330R; R0805
R109, R110, R118: 47K; R0805
R111, R117: 750R; R0805
R112: 1K; R0805
R113: 2K2; R0805
R114, R115: 10K; R0805
R116: 1R; R0805
R120: 470R; R0805
R121: 100K; R0805
X3: 1844249; MC1,5/5-G-3,5
X4: ZL263-20DG; SSW-110-02-T-D-RA

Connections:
+5V: D16.C, K1.1 (+), LED1.BA (A), R114.2; also elsewhere on the board
GND: Q22.E, Q24.E, Q26.2 (S), R109.1, R118.1, R121.1; also elsewhere on the board
unnamed: C86.2, Q23.B, R108.1, R111.2, R113.2
unnamed: C87.2, Q23.C, R110.1, R115.2
unnamed: Q25.C, R112.1
unnamed: C95.1, Q25.B, R117.1, R119.2
unnamed: C87.1, Q22.B, R109.2, R110.2
unnamed: Q24.B, R115.1, R118.2
unnamed: C88.2, R116.2
unnamed: D16.A, K1.8 (-), Q26.3 (D), R120.1
unnamed: K1.4 (S), X3.4
unnamed: K1.5 (S), X3.5
unnamed: LED1.BC (C), R120.2
unnamed: R112.2, R113.1
OUTC+: C90.1, C91.+, C92.1, C93.1, J2.1, J2.NC1, J2.NC2, J2.NC3, J2.NC4, X4.1, X4.2, X4.3, X4.4, X4.5
OUTC-: C91.-, C92.2, C93.2, C94.2, J3.1, J3.NC1, J3.NC2, J3.NC3, J3.NC4, X4.16, X4.17, X4.18, X4.19, X4.20
OUTF+: F2.2, X4.6, X4.7, X4.8, X4.9, X4.10; also elsewhere on the board
PE: C90.2, C94.1, X3.3; also elsewhere on the board
POST_OUT+: F1.1; also elsewhere on the board
POST_OUT-: C89.-, C95.2, D15.1 (A), D15.2 (A), JP4.1, K1.7 (O), Q25.E, R116.1, R119.1, X4.11, X4.12, X4.13, X4.14, X4.15; also elsewhere on the board
POST_OUTF+: C86.1, C88.1, C89.+, D15.3 (C), F1.2, F2.1, JP3.2, K1.2 (O), Q23.E, R108.2
RSENSE: Q26.1 (G), R121.2; also elsewhere on the board
SENSE+: JP3.1, K1.3, R111.1; also elsewhere on the board
SENSE-: JP4.2, K1.6, R117.2; also elsewhere on the board
SENSE_ERR: Q24.C, R114.1; also elsewhere on the board
SENSE_PROT: Q22.C; also elsewhere on the board

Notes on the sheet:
Rsense polarity protection Output coupling, Rsense relay
Licensed under the TAPR Open Hardware License (www.tapr.org/OHL)
Repository: https://github.com/eez-open
More info at http://www.envox.hr/eez
Remote sense reverse polarity detection
Remote sense selection
Output coupling connector (via Backplane PCB)
Power output section

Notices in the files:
parts and their libraries:
EEZ_DIB: This work is licensed under the TAPR Open Hardware License.
